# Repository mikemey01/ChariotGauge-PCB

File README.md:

# ChariotGauge-PCB
All of the gerber files for creating a Chariot Gauge PCB controller yourself.

# Build Your Own
The latest iteration of the controller is in the Version 2 folder. These are all of the gerber files needed to build your own controller from any PCB MFG. The chariotgaugev2.zip contains only the necessary files that any PCB mfg would need.

I use and recommend Advanced Circuits.

Steps for assembling the controller can be found here: https://www.chariotgauge.com/install-guide-diy/

# Modify
If you want to modify the PCB I've included the board and schematic files from Eagle CAD. You'll need to install Eagle CAD to view/edit the schematics.

# Chariot Gauge DIY
There are three parts to the Chariot Gauge project, this is the PCB repo:
* [Chariot Gauge Controller Firmware](https://github.com/mikemey01/ChariotGauge-Firmware)
* [Chariot Gauge Controller](https://github.com/mikemey01/ChariotGauge-PCB)
* [Chariot Gauge Android App](https://github.com/mikemey01/ChariotGaugeAndroid), or [Chariot Gauge iOS App](https://github.com/mikemey01/ChariotGaugeiOS)

# License

MIT License

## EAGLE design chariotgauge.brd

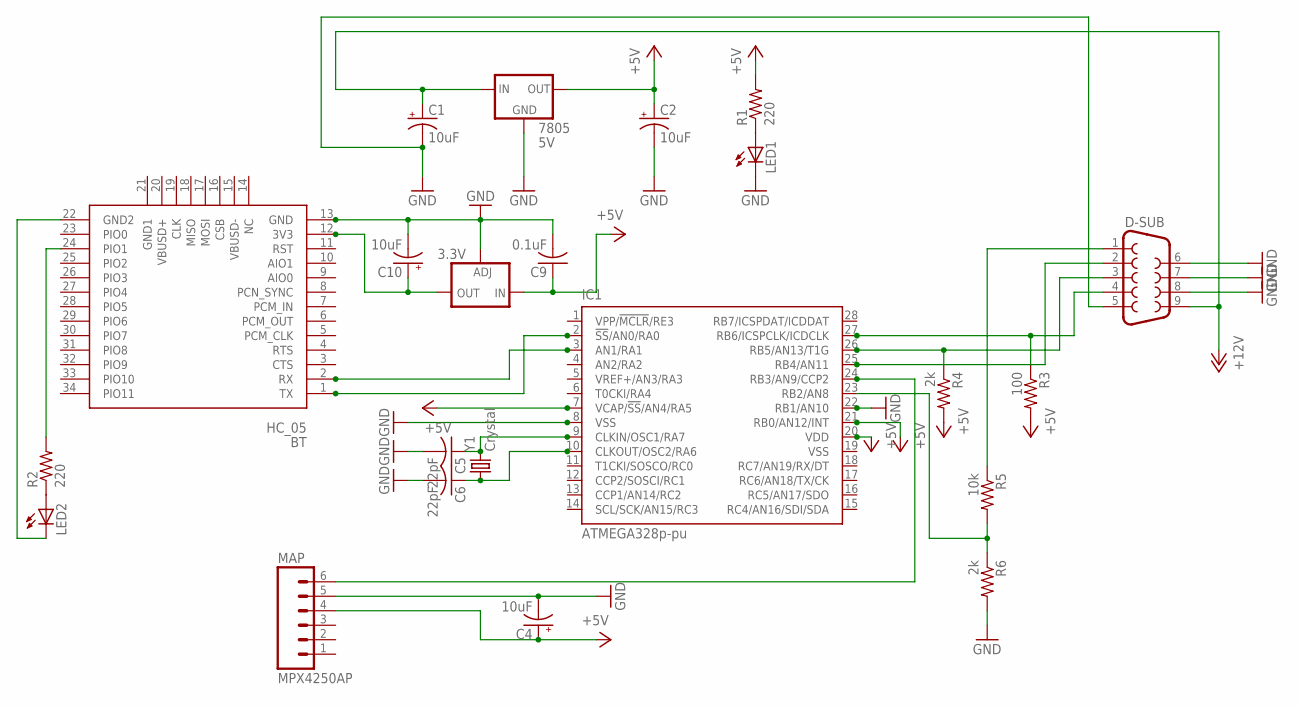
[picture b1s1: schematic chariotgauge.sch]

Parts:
3.3V: LM317TL; 317TL
7805: 5V; 78XXL
BT: HC_05; BLUETOOTH_SMD
C1, C2, C4, C10: 10uF; CPOL-RADIAL-10UF-25V
C5, C6: 22pF; C025-025X050
C9: 0.1uF; C025-025X050
D-SUB: DB9FEMALE; DB9
IC1: ATMEGA328p-pu; DIL28-3
LED1, LED2: LED5MM
MAP: MPX4250AP; 1X06_LONGPADS
R1, R2: 220; 0204/7
R3: 100; 0204/7
R4, R6: 2k; 0204/7
R5: 10k; 0204/7
Y1: Crystal; HC49US

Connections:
+5V: 3.3V.3 (IN), 7805.OUT, C2.1 (+), C4.1 (+), C9.1, IC1.7 (VCAP/!SS!/AN4/RA5), IC1.20 (VDD), IC1.21 (RB0/AN12/INT), MAP.4, R1.2, R3.2, R4.2
+12V: 7805.IN, C1.1 (+), D-SUB.9
GND: 3.3V.1 (ADJ), 7805.GND, BT.13 (GND), C1.2 (-), C2.2 (-), C4.2 (-), C5.2, C6.2, C9.2, C10.2 (-), D-SUB.5, D-SUB.6, D-SUB.7, D-SUB.8, IC1.8 (VSS), IC1.22 (RB1/AN10), LED1.K (C), MAP.5, R6.2
unnamed: LED1.A, R1.1
unnamed: IC1.24 (RB3/AN9/CCP2), MAP.6
unnamed: D-SUB.2, IC1.25 (RB4/AN11)
unnamed: BT.1 (TX), IC1.2 (!SS!/AN0/RA0)
unnamed: D-SUB.3, IC1.26 (RB5/AN13/T1G), R4.1
unnamed: BT.24 (PIO1), R2.2
unnamed: D-SUB.4, IC1.27 (RB6/ICSPCLK/ICDCLK), R3.1
unnamed: BT.2 (RX), IC1.3 (AN1/RA1)
unnamed: C5.1, IC1.9 (CLKIN/OSC1/RA7), Y1.2
unnamed: C6.1, IC1.10 (CLKOUT/OSC2/RA6), Y1.1
unnamed: LED2.A, R2.1
unnamed: 3.3V.2 (OUT), BT.12 (3V3), C10.1 (+)
unnamed: D-SUB.1, R5.1
unnamed: BT.22 (GND2), LED2.K (C)
unnamed: IC1.23 (RB2/AN8), R5.2, R6.1
VSS: IC1.19 (VSS)

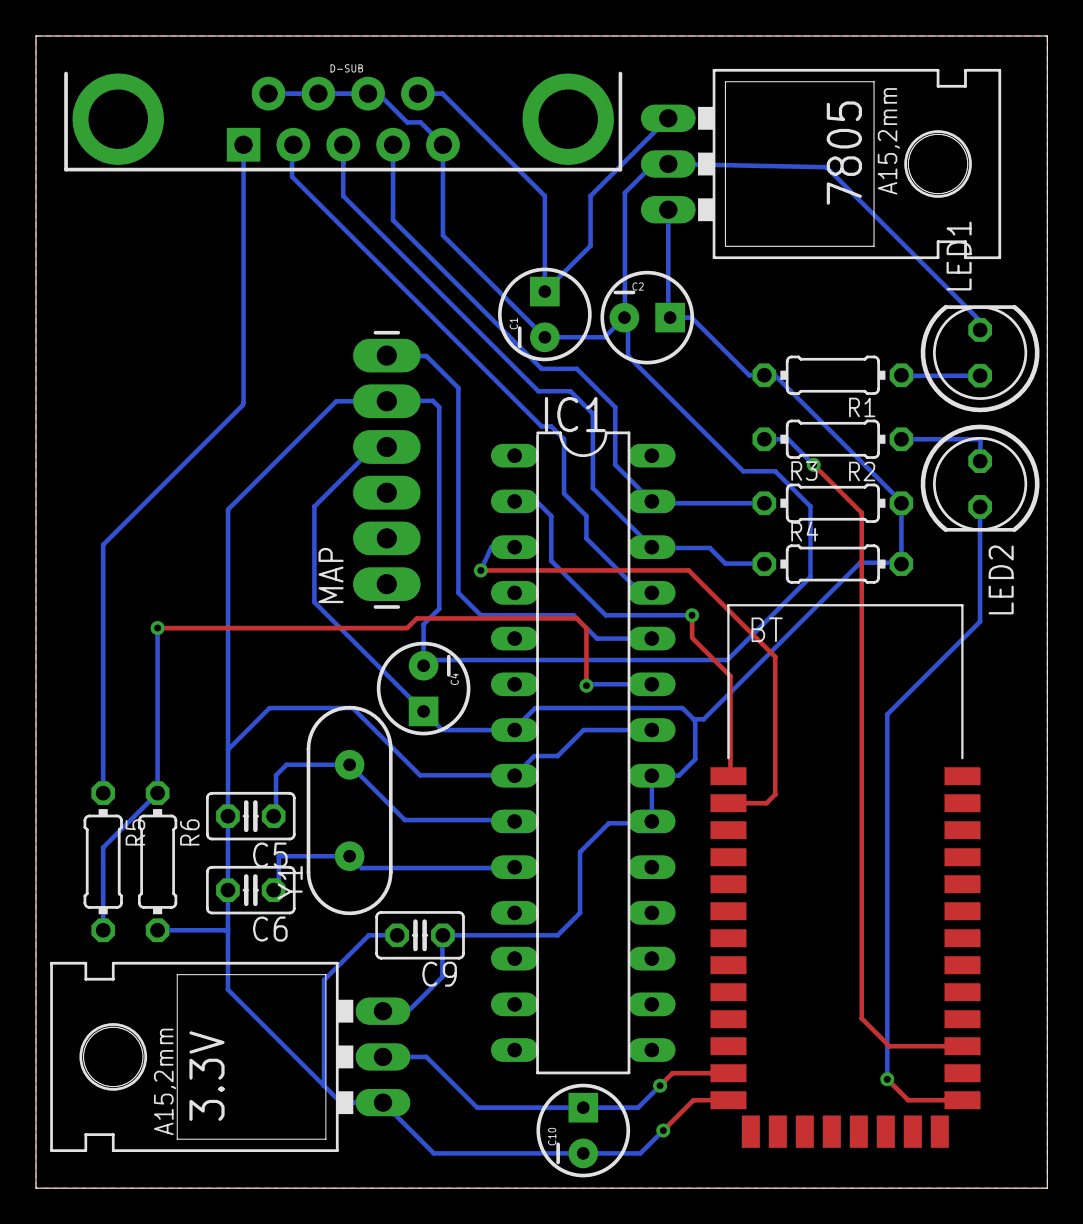
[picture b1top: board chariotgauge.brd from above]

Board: 2 copper layers, 56.2 x 64.0 mm, 22 parts (0 on the bottom side), 18 nets.

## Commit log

2016-05-01 initial commit of PCB files
2016-05-01 readme updates

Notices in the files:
parts and their libraries:
SparkFun-FreqCtrl: Licensing: CC v3.0 Share-Alike You are welcome to use this library for commercial purposes.
